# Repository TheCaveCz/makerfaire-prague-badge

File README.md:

# makerfaire-prague-badge

V tomto repozitáři najdete všechy zdrojové kódy k hardwarovému badge z MakerFaire Prague 2018.

Repozitář má několik částí:

* [Arduino IDE projekt](badge)
* [Schéma pro EAGLE](eagle)
* [Hromadný upload firmware přes USBasp](upload)
* [Programování krok za krokem](programming) - podrobná příručka, jak badge přeprogramovat pomocí Arduino IDE

*Jsme hodně zvědaví, co se vám všechno s badgem podaří vymyslet. Nenechávejte si vaše prográmky jenom pro sebe, klidně je pošlete na info@thecave.cz, rádi je tu zveřejníme!*

## Jak badge vypadá

## Poděkování

Výrobu badgů sponzorovalo [Seeed Studio](https://www.seeedstudio.com).

Badges were sponsored by [Seeed Studio](https://www.seeedstudio.com).

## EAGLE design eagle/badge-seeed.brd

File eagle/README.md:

## Schéma

[Plná velikost](https://raw.githubusercontent.com/TheCaveCz/makerfaire-prague-badge/master/eagle/schematic.png)

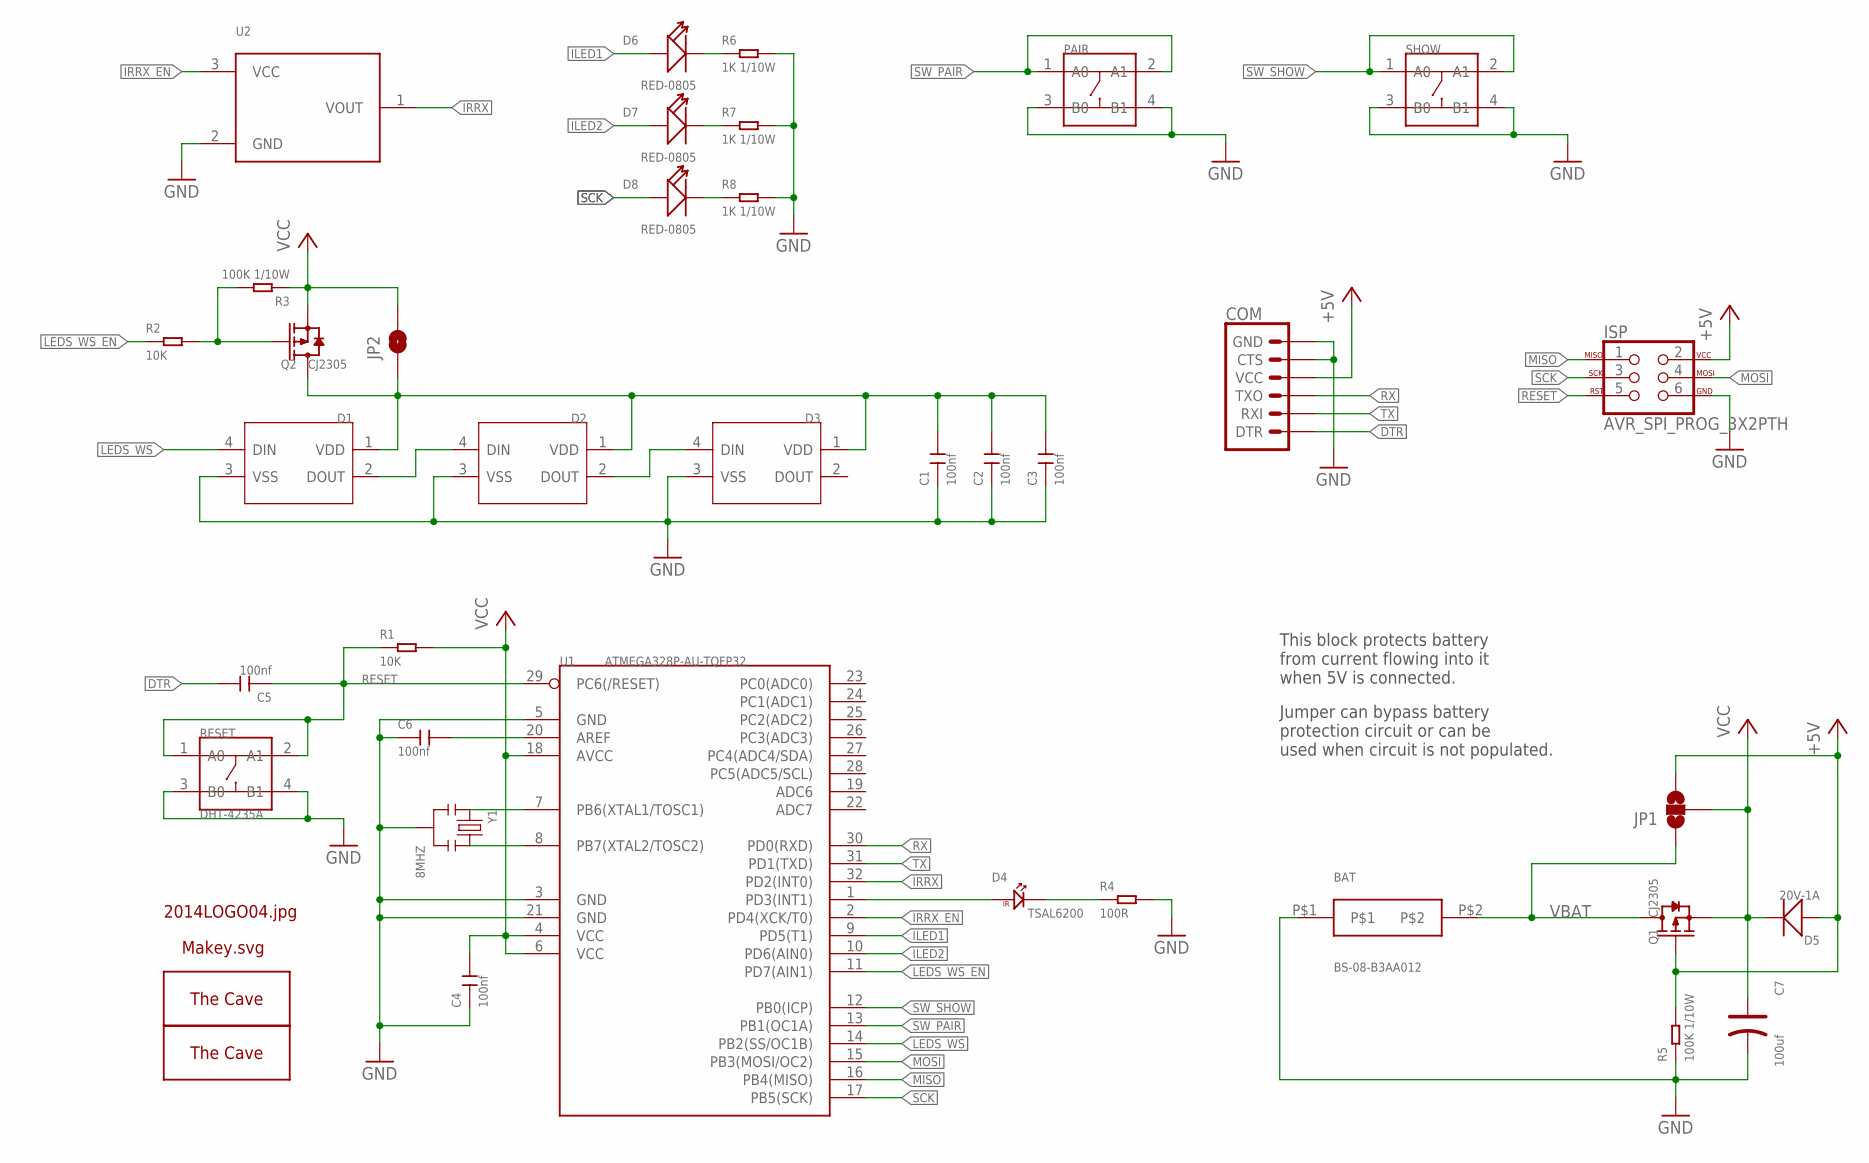
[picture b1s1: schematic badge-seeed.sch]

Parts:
BAT: BS-08-B3AA012; B3-08-B3AA012
C1, C2, C3, C4, C5, C6: 100nf; C0603
C7: 100uf; AVX-B
COM: 6_PIN_SERIAL_TARGETSILK; 6_PIN_SERIAL_TARGET_SIDE_W_SILK
D1, D2, D3: SMD-RGB-LED-4P'WS2812B'; LED4-SMD-5050
D4: TSAL6200
D5: 20V-1A; SOD-123
D6, D7, D8: RED-0805; LED-0805
ISP: AVR_SPI_PROG_3X2PTH; 2X3
JP1: JUMPER-SMT_3_NO_SILK; SMT-JUMPER_3_NO_SILK
JP2: JUMPER-SMT_2_NO_SILK; SMT-JUMPER_2_NO_SILK
PAIR: SMD-BUTTON(4P-5.2X5.2X1.5MM-SKQGADE010)-SKQGADE010; SW4-SMD-5.2X5.2X1.5MM
Q1, Q2: CJ2305; SOT-23
R1, R2: 10K; R0603
R3, R5: 100K 1/10W; R0603
R4: 100R; R0805
R6, R7, R8: 1K 1/10W; R0603
RESET: DHT-4235A; SW4-SMD-4.2X3.2X2.5MM
SHOW: SMD-BUTTON(4P-5.2X5.2X1.5MM-SKQGADE010)-SKQGADE010; SW4-SMD-5.2X5.2X1.5MM
U1: ATMEGA328P-AU-TQFP32; TQFP32-0.8-7X7MM
U2: TSOP382
U$1: 2014LOGO04#JPG
U$2: MAKEY#SVG
U$3: THECAVE_LOGO_TOP_SMALL; LOGO_TOP_SMALL
U$4: THECAVE_LOGO_COPPER_TEXT; LOGO_COPPER_TEXT
Y1: 8MHZ; X3-SMD-3.6X1.3X0.8MM

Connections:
+5V: COM.P$4 (VCC), D5.+, ISP.2, JP1.3, Q1.1 (G), R5.2
DTR: C5.2, COM.P$1 (DTR)
GND: BAT.P$1, C1.1, C2.1, C3.1, C4.1, C6.1, C7.-, COM.P$5 (CTS), COM.P$6 (GND), D1.3 (VSS), D2.3 (VSS), D3.3 (VSS), ISP.6, PAIR.3 (B0), PAIR.4 (B1), R4.2, R5.1, R6.2, R7.2, R8.2, RESET.3 (B0), RESET.4 (B1), SHOW.3 (B0), SHOW.4 (B1), U1.3 (GND), U1.5 (GND), U1.21 (GND), U2.2 (GND), Y1.2
ILED1: D6.+, U1.9 (PD5(T1))
ILED2: D7.+, U1.10 (PD6(AIN0))
IRRX: U1.32 (PD2(INT0)), U2.1 (VOUT)
IRRX_EN: U1.2 (PD4(XCK/T0)), U2.3 (VCC)
LEDS_WS: D1.4 (DIN), U1.14 (PB2(SS/OC1B))
LEDS_WS_EN: R2.1, U1.11 (PD7(AIN1))
MISO: ISP.1, U1.16 (PB4(MISO))
MOSI: ISP.4, U1.15 (PB3(MOSI/OC2))
unnamed: D1.2 (DOUT), D2.4 (DIN)
unnamed: D2.2 (DOUT), D3.4 (DIN)
unnamed: D7.-, R7.1
unnamed: U1.7 (PB6(XTAL1/TOSC1)), Y1.1
unnamed: U1.8 (PB7(XTAL2/TOSC2)), Y1.3
unnamed: D4.N, R4.1
unnamed: C6.2, U1.20 (AREF)
unnamed: D6.-, R6.1
unnamed: D8.-, R8.1
unnamed: C1.2, C2.2, C3.2, D1.1 (VDD), D2.1 (VDD), D3.1 (VDD), JP2.1, Q2.3 (D)
unnamed: D4.P, U1.1 (PD3(INT1))
unnamed: Q2.1 (G), R2.2, R3.2
RESET: C5.1, ISP.5, R1.1, RESET.1 (A0), RESET.2 (A1), U1.29 (PC6(/RESET))
RX: COM.P$2 (TXO), U1.30 (PD0(RXD))
SCK: D8.+, ISP.3, U1.17 (PB5(SCK))
SW_PAIR: PAIR.1 (A0), PAIR.2 (A1), U1.13 (PB1(OC1A))
SW_SHOW: SHOW.1 (A0), SHOW.2 (A1), U1.12 (PB0(ICP))
TX: COM.P$3 (RXI), U1.31 (PD1(TXD))
VBAT: BAT.P$2, JP1.1, Q1.3 (D)
VCC: C4.2, C7.+, D5.-, JP1.2, JP2.2, Q1.2 (S), Q2.2 (S), R1.2, R3.1, U1.4 (VCC), U1.6 (VCC), U1.18 (AVCC)

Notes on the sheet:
This block protects battery from current flowing into it when 5V is connected.
Jumper can bypass battery protection circuit or can be used when circuit is not populated.

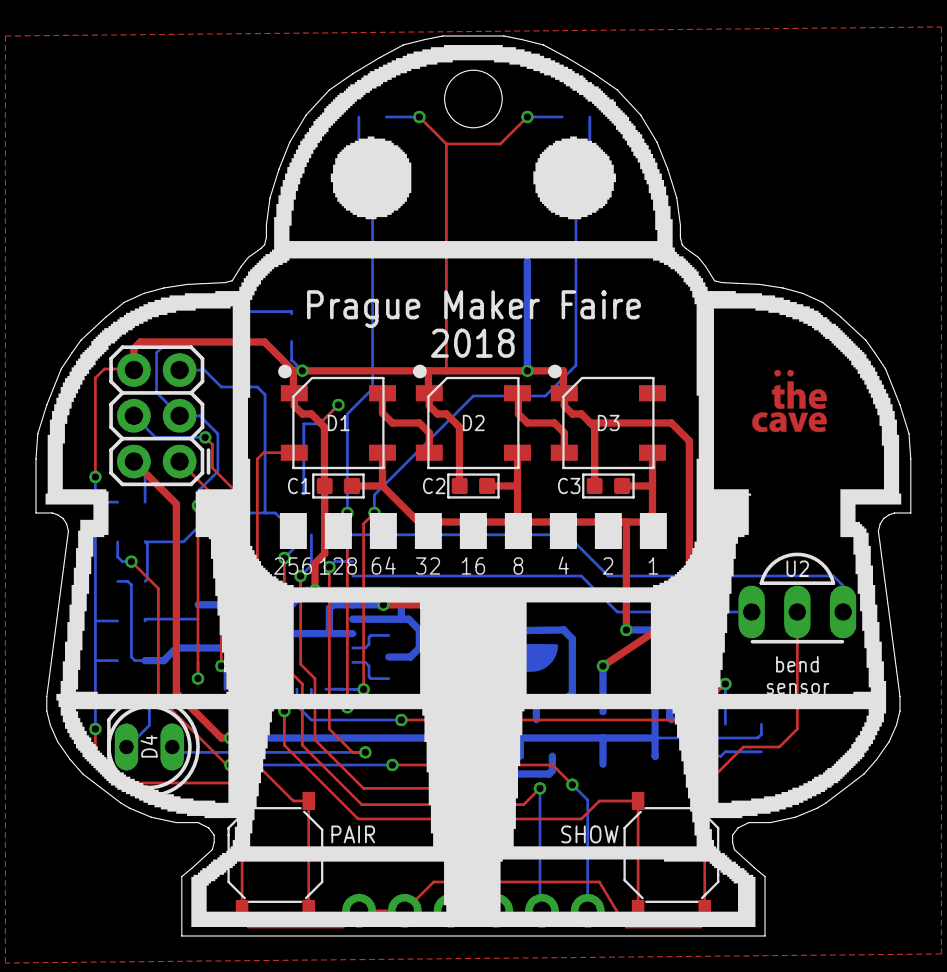
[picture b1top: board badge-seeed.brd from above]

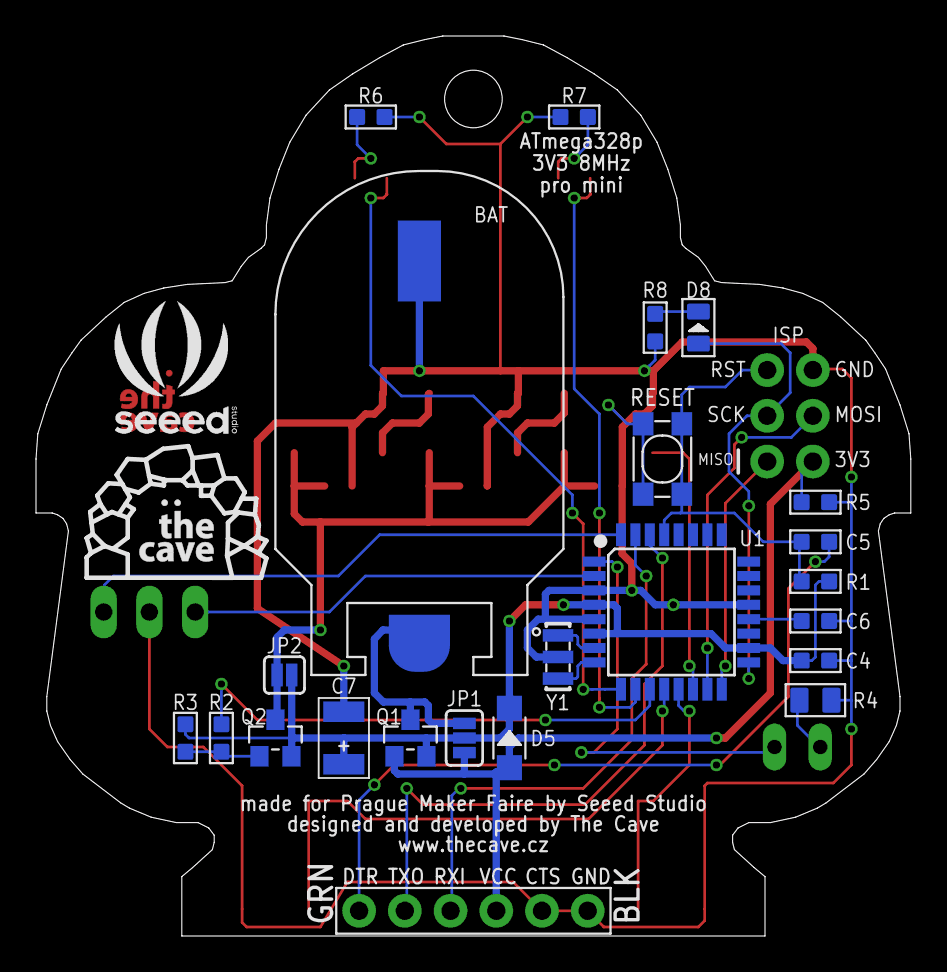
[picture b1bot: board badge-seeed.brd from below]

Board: 2 copper layers, 48.6 x 50.0 mm, 40 parts (25 on the bottom side), 31 nets.

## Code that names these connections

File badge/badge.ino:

//////////////////////////////
//
// MakerFaire Prague 2018 badge
// (c) The Cave, 2018
// https://thecave.cz
//
// Licensed under MIT License.
//
// (written in a very short time and without a lot of sleep)
// 
// There are surely lot of ways how this code can be made better, but it works for the specific case we had.
// Lot of assumptions about sizes/commands/behaiours is hardcoded. If you change something, don't be
// surprised that it can break something else.
//
// Use "Arduino Pro or Pro Mini" board with "ATMega328P (3V3, 8MHz)" setting
//
// But if you change something and it works, feel free to send a pull request!
//
// Happy hacking!
//

#include <EEPROM.h>
#include <TaskScheduler.h>
#include <avr/sleep.h>
#include <avr/power.h>
#include <avr/interrupt.h>

// enable serial line debug info output
#define LOG_ENABLED 1


// Pin Assignments

// PB2 (dip 16) output - data ouput line for WS2818 LEDS
#define PIN_LEDS_WS 10
// PD7 (dip 13) output - gate for P-MOSFET controlling WS2818 VCC line
#define PIN_LEDS_WS_ENABLE 7
// PD4 (dip 6) output - VCC for IR receiver
#define PIN_IRRX_EN 4
// PD2 (dip 4) input - data input line from IR receiver
#define PIN_IRRX 2
// PD3 (dip 5) output - IR led 
#define PIN_IRTX 3
// PD6 (dip 12) output - left eye LED
#define PIN_LED1 6
// PD5 (dip 11) output - right eye LED
#define PIN_LED2 5
// PB5 builtin led - LED on the back of the robot
#define PIN_LED3 13

// both buttons need to be on the same port
// if you change pins you need to change the pin change interrupt regs too!
// PB1 (dip 15) input pullup - PAIR button
#define PIN_SW1 9
// PB0 (dip 14) input pullup - SHOW button
#define PIN_SW2 8


Scheduler scheduler;

// NOTE : you may see function prototypes declarations in the source
// for some reason Arduino IDE fails to generate function prototypes in this source

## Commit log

2018-06-25 Add all source files
2018-07-01 Update badge picture
2018-07-01 Add guide (first part)
2018-07-01 Add guide (second part)

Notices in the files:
parts and their libraries:
SparkFun-Connectors: Licensing: Creative Commons ShareAlike 4.0 International - https://creativecommons.org/licenses/by-sa/4.0
